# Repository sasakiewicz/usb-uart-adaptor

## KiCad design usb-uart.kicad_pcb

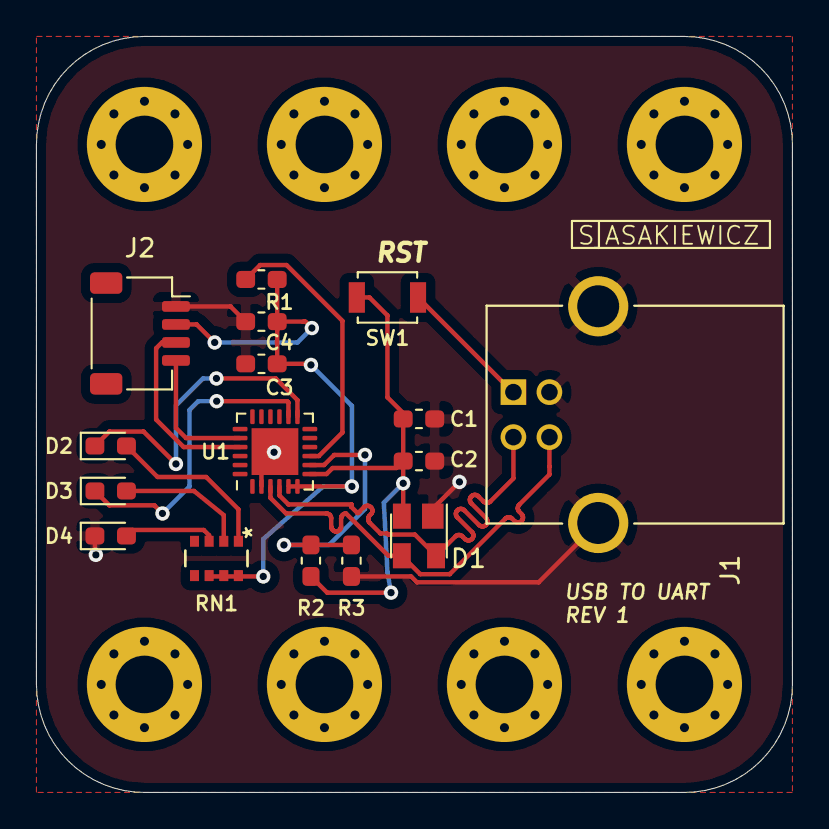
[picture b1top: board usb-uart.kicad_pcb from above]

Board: 2 copper layers, 42.0 x 42.0 mm, 24 parts (0 on the bottom side), 15 nets.

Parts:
C1, C3: 4.7 uF; C_0603_1608Metric_Pad1.05x0.95mm_HandSolder
C2, C4: 0.1 uF; C_0603_1608Metric_Pad1.05x0.95mm_HandSolder
D1: SP0503BAHT; SOT-143
D2, D3, D4: LED; LED_0603_1608Metric_Pad1.05x0.95mm_HandSolder
H1, H2, H3, H4, H5, H6, H7, H8: MountingHole; MountingHole_3.2mm_M3_Pad_Via
J1: USB_B; OST_USB-B1HSB6
J2: Conn_01x04_Female; JST_SH_SM04B-SRSS-TB_1x04-1MP_P1.00mm_Horizontal
R1: 1k; R_0603_1608Metric_Pad1.05x0.95mm_HandSolder
R2: 22.1; R_0603_1608Metric_Pad1.05x0.95mm_HandSolder
R3: 47.5; R_0603_1608Metric_Pad1.05x0.95mm_HandSolder
RN1: EXB-V8V331JV
SW1: SW_Push_Open; SW_SPST_B3U-1000P
U1: CP2102N-A01-GQFN24; QFN-24-1EP_4x4mm_P0.5mm_EP2.6x2.6mm

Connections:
+5V: C1.1, C2.1, D1.2, R2.1, SW1.2, U1.7
GND: C1.2, C2.2, C3.2, C4.2, D1.1, D4.1, J1.4, J1.P1, J1.P2, J2.1, R3.2, U1.2, U1.25
unnamed: C3.1, C4.1, J2.2, R1.1, RN1.6, RN1.7, RN1.8, U1.5, U1.6
unnamed: D1.3, J1.3, U1.3
unnamed: D1.4, J1.2, U1.4
unnamed: D2.1, U1.13
unnamed: D2.2, RN1.1
unnamed: D3.1, U1.14
unnamed: D3.2, RN1.2
unnamed: D4.2, RN1.3
unnamed: J1.1, SW1.1
unnamed: J2.3, U1.21
unnamed: J2.4, U1.20
unnamed: R1.2, U1.9
unnamed: R2.2, R3.1, U1.8

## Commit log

2021-07-12 Rev A Kicad files
2021-10-03 updated to build (and include) a .step 3d model of the board

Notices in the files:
parts and their libraries:
Copyright 2016 Accelerated Designs. All rights reserved.
